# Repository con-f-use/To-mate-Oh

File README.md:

To-mate-Oh
==========

A [pomodoro](http://pomodorotechnique.com/) timer featuring a <a href="https://en.wikipedia.org/wiki/Capacitive_sensing">capacitve touch button</a>, <a href="https://en.wikipedia.org/wiki/Pulse-width_modulation">PWM</a>-driven LEDs and a <a href="https://en.wikipedia.org/wiki/Piezoelectricity#Actuators">piezo buzzer</a>. Based on the <a href="https://github.com/fakufaku/Pomodoro">Pomodoro project</a> by <a href="http://robinscheibler.org">Robin Scheibler</a> (github: <a href="https://github.com/fakufaku">FakuFaku</a>).

*Note: This readme might not always be up to date. Plese consult ./firmware/To-mate-Oh.h and the files in ./docu for more recent information.*

Introduction
------------

I saw the <a href="https://github.com/fakufaku/Pomodoro">POMODORO project</a> by <a href="http://robinscheibler.org">Robin Schreibler</a> and decided to build it. Some may know Robin by the name FakuFaku or from <a href="http://hackaday.com/2014/02/09/hack-all-the-things-in-the-time-you-save-with-this-led-pomodoro-timer/">Hackaday</a>. His' is a very nice layout with beautifully clean code.

__"That can't stand!"__, I thought, so first thing I did was soil the code and complicate the layout. And here is why: I was measuring the power consumption of the original Pomodoro. With a fresh coin cell at 3.3 V, the Pomodoro drained 1.6mA, even when in power down. Your average coin cell has about 200 mAh to give, ignoring the voltage decay. That means after 5 days at most, the battery is gone. This project has since then triggered Robin to fix this bug.

I thought I can do better, and that kind of exploded in my face. Now the board is a quarter of Robin's footprint, has proper reverse polarity protection, drains only about 6 uA (when inactive) and uses less components. Most notably I could do away with four resistors and the switch. The design uses capacitive sensing now and drives the LEDs directly with PWM. The PWM has the added benefit of dimming the LEDs to indicate passed time. You can tweak the duty cycle in code to work with the old hardware (or bridge the unnecessary resistors). On the down side, the code is much, much uglier (but uses only a third of the space on the micro controller). I think it's an improvement, but judge for yourself.

Anyways, many thanks to Robin for making his project open source and being awesome!

Using the Board
---------------

From Robins original documentation (with additions of my own):

1. One click starts a 25 minutes _work_ counter. Five LEDs indicate how many slices of five minutes are left. Every minute the leading led flashes number of times equal to the passed minutes in that slice. It also dims in brightness to indicate the minutes passed. There is a discrete beep when the 25 minute timer expires. The LED then flashes to remind you to go into _rest_ mode.
2. A second click starts a 5 minutes _rest_ counter. The status LED is turned on. There is a discrete beep when it expires. Then the timer turns off.
3. If you wish to turn the timer off during _rest_ mode, click the button a third time.

When you insert a fresh battery, a calibration for the cap sense button is performed. To not touch the upper side of the board during that period. After a successful calibration the To-mate-Oh will circle through its LEDs and beep. If you count the beeps or how often a different LED is lit, it will give you the calibration constant. If the calibration fails, the To-mate-Oh will blink LED2 for five seconds. If this occurs, most likely the sense pad was accidentally connected to a large capacity (e.g. you) or ground.

Making/Ordering the Board
-------------------------

You can order the circuit board at a board house of your choice. e.g. <a href="http://dirtypcbs.com/view.php?share=3243&accesskey=5920ddd4c2010ad6628f47974e820113">Dirty PCBs</a> ($14 to get 20 To-mate-Oh boards). The total price per To-mate-Oh (board + components) should come in at around $3-4. The board is still one sided, but you have to solder the components, break it in two, and sandwich-connect the two halves by soldering them together with solid leads of metal (pin headers work fine). If you live in Germany or Austria, I might be willing to sell you a kit with the board and all components required. Just <a href="mailto:con-f-use@gmx.net?Subject=To-mate-Oh%20Order">contact me</a>.

If you choose to make the board yourself, there are tons of good introductions on <a href="http://hackaday.com/2008/07/28/how-to-etch-a-single-sided-pcb/">how to etch circuit boards</a> at home and <a href="http://store.curiousinventor.com/guides/How_To_Solder"> how to solder</a> (sorry this is pay-for-view now which is very unnerving, try the <a href="https://www.youtube.com/watch?v=b9FC9fAlfQE">EEVBlog tutorial</a>) components to them. With that in mind, the eagle files, pictures and schematics in the ./hardware directory should be all the instructions you need. The coin cell holder is sandwiched between the two halves of the board. You might need to fill the middle trough hole pad under the buzzer with something to make proper contact with the negative contact of the battery on the other side of the board. I listed the components and tools needed below. The components are available e.g. on <a href="https://www.mouser.com/ProjectManager/ProjectDetail.aspx?AccessID=97d69422c2">Mouser</a>. Values and part numbers are only recommendations, use whatever you have. I listed what I used in brackets:

 - Atmel AtTiny25/45/85 microcontroller
 - 5x LED all one color, SMD 0805 (VLMB1300-GS08)*
 - 1x LED any other color, SMD 0805 (VLMS1300-GS08)*
 - 2x 3.3 k Ohm Resistor, SMD 0805[^1]
 - 1x NPN BJT transistor, SOT-23 (BC857)[^2]
 - 1x 220uH Inductor, SMD 1007
 - 1x Buzzer, SMD (Kobitone 254-PB119-ROX)
 - 1x CR2032 coin cell and holder
 - A bit of solid core wire, pin headers or component leads
 - Optional:
    - 1x MOSFET P-Channel, SOT-23 (SI2371ESD)[^3]
    - 1x 1-10 uF Capacitor, SMD 1210[^4]

__Warning: *If you use LEDs other than the Vishay 1300 series, you might get differences in brightness or in very rare cases damage the ATTiny. The LEDs are PWM-dimmed with no current limiting resistor. Not all LEDs have the same efficiency and forward voltage. Current through them may vary. And even at same current, the brightness may vary. The ATTiny must only supply up to 40mA max per output pin and only sink 10mA per input. Additionally all inputs together must not sink more than 60mA (150 mA source per output). A regular CR2032 can provide as muchs as 300mA of current. At the low duty cycles in the program and 3.3V supply voltage from the battery there should be no problem no matter the LEDs. But if you use non-standard LEDs or supply the circuit with more than 3.3V, e.g. when programming, give it a thought or two and consult the <a href="http://www.atmel.com/images/atmel-2586-avr-8-bit-microcontroller-attiny25-attiny45-attiny85_datasheet.pdf">ATTiny's datasheet</a>.__

Tools for soldering:

- Good soldering ion with small tip for SMD soldering
- Third hand tool
- Wire cutter
- Programmer for the micro controller (e.g. <a href="http://www.geppettoelectronics.com/2014/08/usb-isp-user-guide.html">USB μISP</a>)
- <a href="http://www.tag-connect.com/">Tag connect adapter</a> [^5]

If you are making the board yourself (so you really don't want to order it?):

- Laser printer
- Dremel or similar tool for drilling small holes
- Tool to cut your copper clad board (for thin material -> scissors)
- Cloth iron or laminator (or UV photo resist, developer, transparencies and UV exposure unit)
- Etchant resistant container
- Tab water
- Workspace and clothing that don't mind dirt and discoloration
- __Etchant resistant Gloves__
- __Safety glasses__

__Warning: Etching circuit boards involves corrosive chemicals with the usual dangers (eye damage, chemical burns, damage to the respiratory system, damage to the environment and surroundings, etc.). Know what you're are doing!__

Compiling and flashing the firmware
-----------------------------------

```bash
# Under Ubuntu running these in the ./firmware directory should do:
sudo apt-get install
sudo apt-get install gcc-avr avrdude avr-libc
make flashfuse
```

To flash the firmware to the micro controller run "make flashfuse" after you connected the ISP header on the board to your programmer. The board does not connect the Tag Connect's positive voltage pin to the micro controller. The power pin of your programmer will have to be connected manually to the battery holder's positive contact. This is to avoid exposing an inserted battery to the USB voltage, so **before programming, take the battery out and connect positive voltage yourself.**

The firmware for this project requires avr-gcc and avr-libc (a C-library for the AVR micro controllers). Please read the instructions on how to <a href="http://www.nongnu.org/avr-libc/user-manual/install_tools.html">install the GNU toolchain for avr</a> (avr-gcc, assembler, avr-libc, linker, make, etc.) if above command's did not work for you. Additionally, <a href="http://www.ladyada.net/learn/avr/index.html">Lady Ada's avr tutorial</a> covers the basics of flashing firmware to a micro controller nicely. Running "make flashfuse" in the ./firmware direcotry should be sufficient. You will have to edit the "DEVICE" variable in the Makefile to reflect of the ATTiny25/45/85s you are using. If you are using a programmer other than a <a href="http://www.ladyada.net/make/usbtinyisp/">USBtinyISP</a> variant (btw.: you can build USBtinyISP at home) you need to edit that into the Makefile as well.

If you change the firmware or fuse bits, be aware that the cap sensing and led timing is very sensitive. In the ./firmware/To-mate-Oh.h are a few settings related to LED PWM and timeouts (scroll way down in the .h file until after this documentation).

*Note: There is much room for optimization. For instance, one could get rid of the delays by using a timer for the short led pulses and putting the controller to sleep for the long ones (the watchdog timer can go down to 15 ms). The watchdog timer is not that accurate and temperature stable though. Speaking of accuracy, the delay lengths could be adjusted for more accurate timing.*

Copyright
---------

This file is part of the To-mate-Oh project. Copyright © 2014 con-f-use. Use permitted under GNU General Public License (see LICENSE.txt).

To-mate-Oh is based on the Pomodoro timer by Robin Scheibler (FakuFaku). See <http://robinscheibler.org> and <https://github.com/fakufaku/Pomodoro> for more details on the original project.

To-mate-Oh is a free electronics project: you can redistribute it and/or  modify it under the terms of the GNU General Public License as published by the Free Software Foundation, either version 3 of the License, or (at your option) any later version.

To-mate-Oh is distributed in the hope that it will be useful, but WITHOUT ANY WARRANTY; without even the implied warranty of MERCHANTABILITY or FITNESS FOR A PARTICULAR PURPOSE. See the GNU General Public License for more details.

You should have received a copy of the GNU General Public License along with To-mate-Oh. If not, see <http://www.gnu.org/licenses/>.

The following files comprise To-mate-Oh: ./docu/docu.pdf, ./docu/doxygen.cfg, ./docu/doxygen.sh, ./firmware/Makefile, ./firmware/To-mate-Oh.c, ./firmware/To-mate-Oh.h, ./hardware/To-mate-Oh.brd, ./hardware/To-mate-Oh.sch, ./hardware/To-mate-Oh-board.png, ./hardware/To-mate-Oh-etch.pdf, ./hardware/To-mate-Oh-schematic.pdf, ./hardware/To-mate-Oh-prototype.jpg, ./hardware/To-mate-Oh-final.jpg, ./hardware/To-mate-Oh-kit.jpg, ./hardware/To-mate-Oh-panel.gerber.zip, ./LICENSE.txt, ./README.md

Their use is permitted under the terms of GNU General Public License as well. If you want to use any part under different terms, please feel free to ask the author for his permission.

[^1]: The 3k3 resistor on the base of the NPN shouldn't be lower or it might interfere with programming.
[^2]: The NPN can be pretty generic but should be able to stomach the spikes created by the inductor.
[^3]: The P-MOS should have a threshold voltage well below the battery voltage to work as reverse polarity protection. A low on resistance is nice, too. If you don't use it, short source and drain together. The SI2371ESD is nice because it includes TVS diodes for ESD protection.
[^4]: The 10uF cap is a good thing to enhance battery life by smoothing out peak drains/spikes. It is however not necessary.
[^5]: The tag connect adapter is only needed if you don't want to solder temporary wires for programming. It has a much smaller footprint and some other advantages. Some people have build clones.You could also program the chip off board.

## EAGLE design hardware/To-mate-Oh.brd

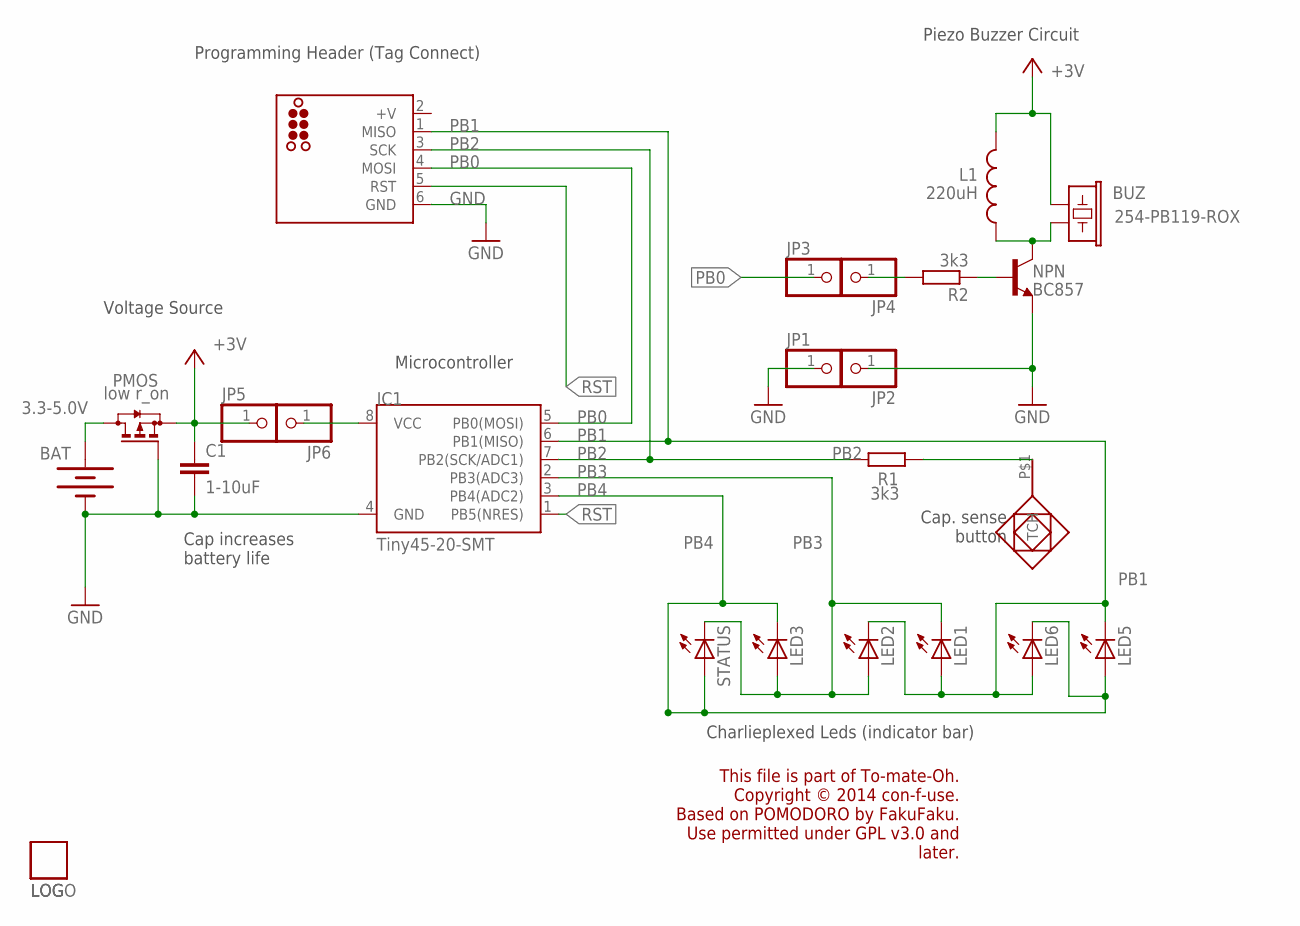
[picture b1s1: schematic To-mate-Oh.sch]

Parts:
BAT: 3.3-5.0V; BATTERY_20MM_PTH_COMPACT
BUZ: 254-PB119-ROX; BUZZER-CMT1102
C1: 1-10uF; C1210
CAP_SENSE: PAD; EMPTY
IC1: Tiny45-20-SMT; SO08-EIAJ
ISP: ATMEL-ISPATMEL_ISP_TC2030; TC2030-MCP-NL
JP1: JGND1; 1X01
JP2: JGND2; 1X01
JP3: JPB1; 1X01
JP4: JPB2; 1X01
JP5: JVCC1; 1X01
JP6: JVCC2; 1X01
L1: 220uH; 1007
LED1, LED2, LED3, LED5, LED6: Blue; CHIPLED_0805
LOG: UNETHILOGO; UNETHILOGO_TINY_SILK
LOGO: UNETHILOGOUNETHILOGO_TINY; UNETHILOGO_TINY
NPN: BC857; SOT23-BEC
PMOS: low r_on; SOT23
R1, R2: 3k3; R0805
STATUS: Red; CHIPLED_0805

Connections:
+V: ISP.2 (+V)
BAT+: BAT.1 (+), BAT.1@2 (+), PMOS.3 (D)
BTN: CAP_SENSE.P$1, R1.2
GND: BAT.2 (-), C1.2, IC1.4 (GND), ISP.6 (GND), JP1.1, JP2.1, NPN.E, PMOS.1 (G)
unnamed: JP4.1, R2.2
unnamed: NPN.B, R2.1
unnamed: IC1.8 (VCC), JP6.1
unnamed: BUZ.2, L1.1, NPN.C
PB0: IC1.5 (PB0(MOSI)), ISP.4 (MOSI), JP3.1
PB1: IC1.6 (PB1(MISO)), ISP.1 (MISO), LED1.A, LED2.C, LED5.C, LED6.A
PB2: IC1.7 (PB2(SCK/ADC1)), ISP.3 (SCK), R1.1
PB3: IC1.2 (PB3(ADC3)), LED1.C, LED2.A, LED3.A, STATUS.C
PB4: IC1.3 (PB4(ADC2)), LED3.C, LED5.A, LED6.C, STATUS.A
RST: IC1.1 (PB5(NRES)), ISP.5 (RST)
VCC: BUZ.1, C1.1, JP5.1, L1.2, PMOS.2 (S)

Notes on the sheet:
Programming Header (Tag Connect)
Piezo Buzzer Circuit
Charlieplexed Leds (indicator bar)
Microcontroller
Voltage Source
Cap. sense button
This file is part of To-mate-Oh. Copyright © 2014 con-f-use. Based on POMODORO by FakuFaku. Use permitted under GPL v3.0 and later.
Cap increases battery life

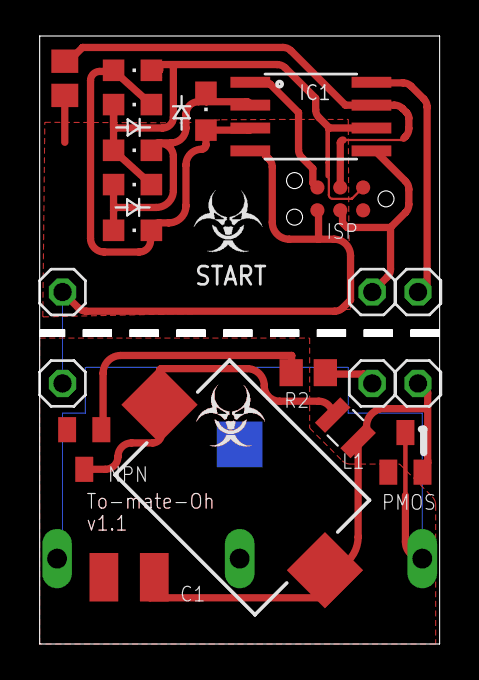
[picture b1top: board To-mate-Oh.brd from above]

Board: 2 copper layers, 22.2 x 33.4 mm, 25 parts (1 on the bottom side), 14 nets.

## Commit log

2015-05-24 To-mate-Oh initial commit
2015-05-26 Added readme
    Update README.md
    Update README.md
    Update README.md
    Update README.md
    Update README.md
    Minor cosmetics
2016-02-14 Create gh-pages branch via GitHub

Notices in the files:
hardware/To-mate-Oh.brd:
General Public License v3.0
parts and their libraries:
SparkFun-Electromechanical: Licensing: Creative Commons ShareAlike 4.0 International - https://creativecommons.org/licenses/by-sa/4.0
jcgb: ©2009 ROFA.cz - modified and updated by Robert Darlington ‹rdarlington@gmail.com›
